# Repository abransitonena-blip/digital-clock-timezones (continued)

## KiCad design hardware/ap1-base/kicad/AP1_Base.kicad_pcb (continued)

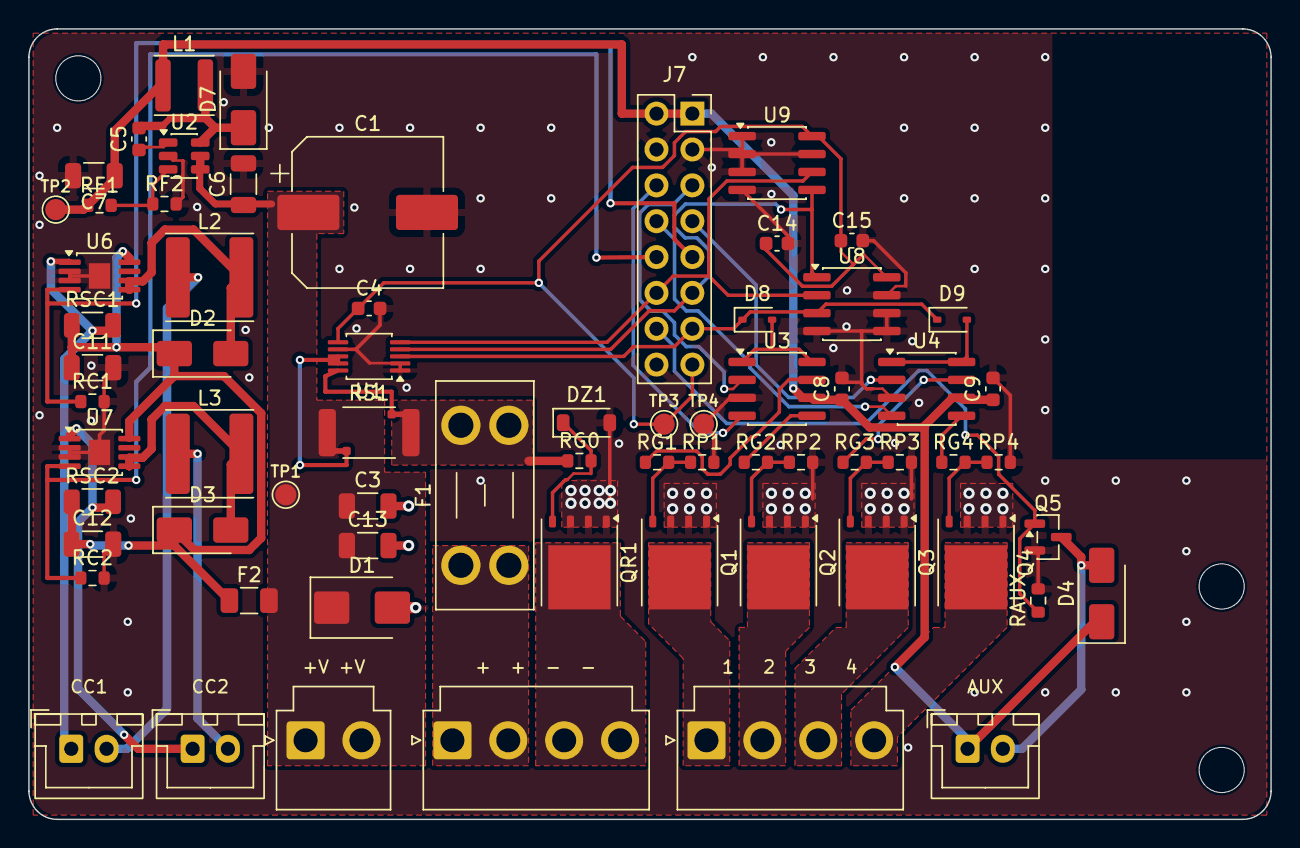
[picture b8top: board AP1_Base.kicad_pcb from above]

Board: 4 copper layers, 88.0 x 56.0 mm, 71 parts (0 on the bottom side), 45 nets.

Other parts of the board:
H1, H2, H3: MountingHole_3.2mm_M3
